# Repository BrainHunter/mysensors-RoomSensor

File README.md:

# mysensors-RoomSensor
Firmware for the RoomSensor

To build this Firmware you need this Arduino Packages:
* mysensors v2.0
* DHT
* SparkFunBME280
* SI7021

Select the Board "NK-Tronic RoomSensor" and Processor: "ATmega328 (3.3V, 8Mhz RC)"

Install the firmware on the board with a ISP programmer like the STK500 or USBasp.

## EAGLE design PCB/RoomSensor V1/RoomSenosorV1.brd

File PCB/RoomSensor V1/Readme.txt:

First version PCB. This one has some Errors:

- Missing connection in the switching supply
- Wrong footprint for the AP3015. (Too small)

	--> PCB's are usable with some solder skills ;-)

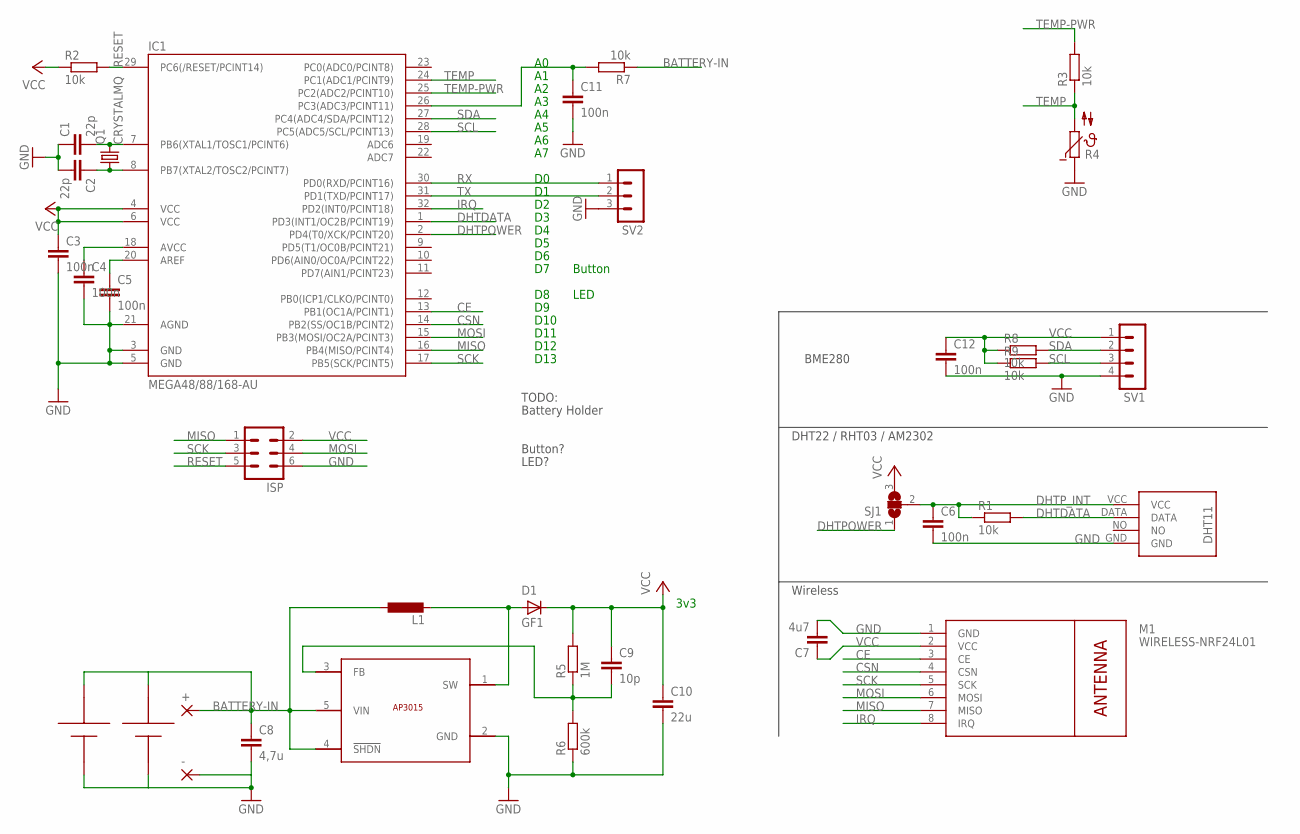
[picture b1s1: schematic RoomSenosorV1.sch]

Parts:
+: 1,6/0,8
-: 1,6/0,8
C1, C2: 22p; C0805
C3, C4, C5, C6, C11, C12: 100n; C0805
C7: 4u7; C0805
C8: 4,7u; C0805
C9: 10p; C0805
C10: 22u; C1206
D1: GF1; SMA-DO214AC
IC1: MEGA48/88/168-AU; TQFP32-08
ISP: MA03-2
L1: L-EUL2825P; L2825P
M1: WIRELESS-NRF24L01
Q1: CRYSTALMQ; MQ
R1, R2, R3, R7, R8, R9: 10k; R0805
R4: NTC640; P640
R5: 1M; R0805
R6: 600k; R0805
SJ1: SJ2W; SJ_2
SV1: MA04-1
SV2: MA03-1
U$1: AP3015/A; SOT353
U$2: DHT11
U$3: MIGNON_1
U$4: RS_279-4959

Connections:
BATTERY-IN: +.1, C8.1, L1.1, R7.1, U$1.4 (!SHDN), U$1.5 (VIN), U$3.POS, U$4.POS
BATTERY-IN-LP: C11.1, IC1.26 (PC3(ADC3/PCINT11)), R7.2
CE: IC1.13 (PB1(OC1A/PCINT1)), M1.3 (CE)
CSN: IC1.14 (PB2(SS/OC1B/PCINT2)), M1.4 (CSN)
DHTDATA: IC1.1 (PD3(INT1/OC2B/PCINT19)), R1.2, U$2.DATA
DHTPOWER: IC1.2 (PD4(T0/XCK/PCINT20)), SJ1.1
DHTP_INT: C6.1, R1.1, SJ1.2, U$2.VCC
GND: -.1, C1.1, C2.2, C3.2, C4.2, C5.2, C6.2, C7.2, C8.2, C10.2, C11.2, C12.2, IC1.3 (GND), IC1.5 (GND), IC1.21 (AGND), ISP.6, M1.1 (GND), R4.1, R6.1, SV1.4, SV2.3, U$1.2 (GND), U$2.GND, U$3.NEG, U$4.NEG
IRQ: IC1.32 (PD2(INT0/PCINT18)), M1.8 (IRQ)
MISO: IC1.16 (PB4(MISO/PCINT4)), ISP.1, M1.7 (MISO)
MOSI: IC1.15 (PB3(MOSI/OC2A/PCINT3)), ISP.4, M1.6 (MOSI)
unnamed: C2.1, IC1.8 (PB7(XTAL2/TOSC2/PCINT7)), Q1.P1 (1)
unnamed: C1.2, IC1.7 (PB6(XTAL1/TOSC1/PCINT6)), Q1.P3 (2)
unnamed: C9.2, R5.1, R6.2, U$1.3 (FB)
unnamed: C5.1, IC1.20 (AREF)
unnamed: C4.1, IC1.18 (AVCC)
unnamed: D1.A, L1.2, U$1.1 (SW)
RESET: IC1.29 (PC6(/RESET/PCINT14)), ISP.5, R2.2
RX: IC1.30 (PD0(RXD/PCINT16)), SV2.1
SCK: IC1.17 (PB5(SCK/PCINT5)), ISP.3, M1.5 (SCK)
SCL: IC1.28 (PC5(ADC5/SCL/PCINT13)), R9.2, SV1.3
SDA: IC1.27 (PC4(ADC4/SDA/PCINT12)), R8.2, SV1.2
TEMP: IC1.24 (PC1(ADC1/PCINT9)), R3.1, R4.2
TEMP-PWR: IC1.25 (PC2(ADC2/PCINT10)), R3.2
TX: IC1.31 (PD1(TXD/PCINT17)), SV2.2
VCC: C3.1, C7.1, C9.1, C10.1, C12.1, D1.K (C), IC1.4 (VCC), IC1.6 (VCC), ISP.2, M1.2 (VCC), R2.1, R5.2, R8.1, R9.1, SJ1.3, SV1.1

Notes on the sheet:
D10
D11
D12
D13
3v3
LED
Button
Wireless
DHT22 / RHT03 / AM2302
TODO:
Battery Holder
Button?
LED?
BME280

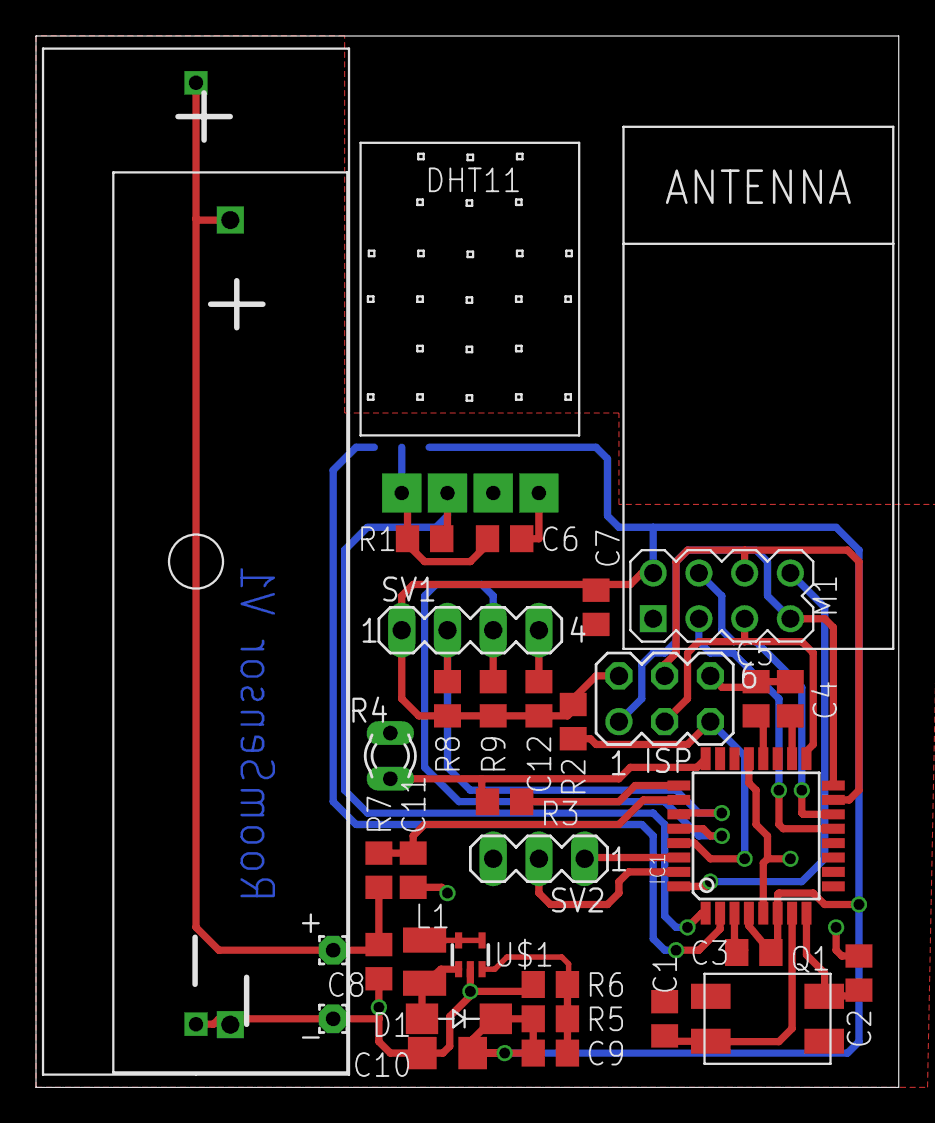
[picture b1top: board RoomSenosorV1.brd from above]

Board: 2 copper layers, 47.9 x 58.4 mm, 36 parts (1 on the bottom side), 26 nets.

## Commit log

2016-10-03 Added PCB version 1 Files
2016-10-09 renamed the ino file Added the Board definition
2016-11-28 Added support for the SI7021. * Changed directory structure.
2016-11-29 Changed code to work with MySensors V2.0 * Code Cleanups / formating
2019-07-27 V1.2: Sketch Info depends on Configuration
2019-08-28 Changed 0% battery voltage from 0.8V to 0.95V

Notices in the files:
parts and their libraries:
diy-modules: Released under the Creative Commons Attribution 4.0 International License: http://creativecommons.org/licenses/by/4.0
